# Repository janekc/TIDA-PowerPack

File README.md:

# TIDA-PowerPack
This board is designed as a prototype for powering your projects using four 18650 lithium-ion battery cells. It delivers a 5V output with a maximum current of 5A. The cells are configured in a 4S1P (4-series, 1-parallel) arrangement, balanced and charged via USB-C Power Delivery (PD) with the maximum charging current supported by the cells.
This design is based on the [TIDA-050047](https://www.ti.com/tool/TIDA-050047#design-products) reference design by Texas Instruments.

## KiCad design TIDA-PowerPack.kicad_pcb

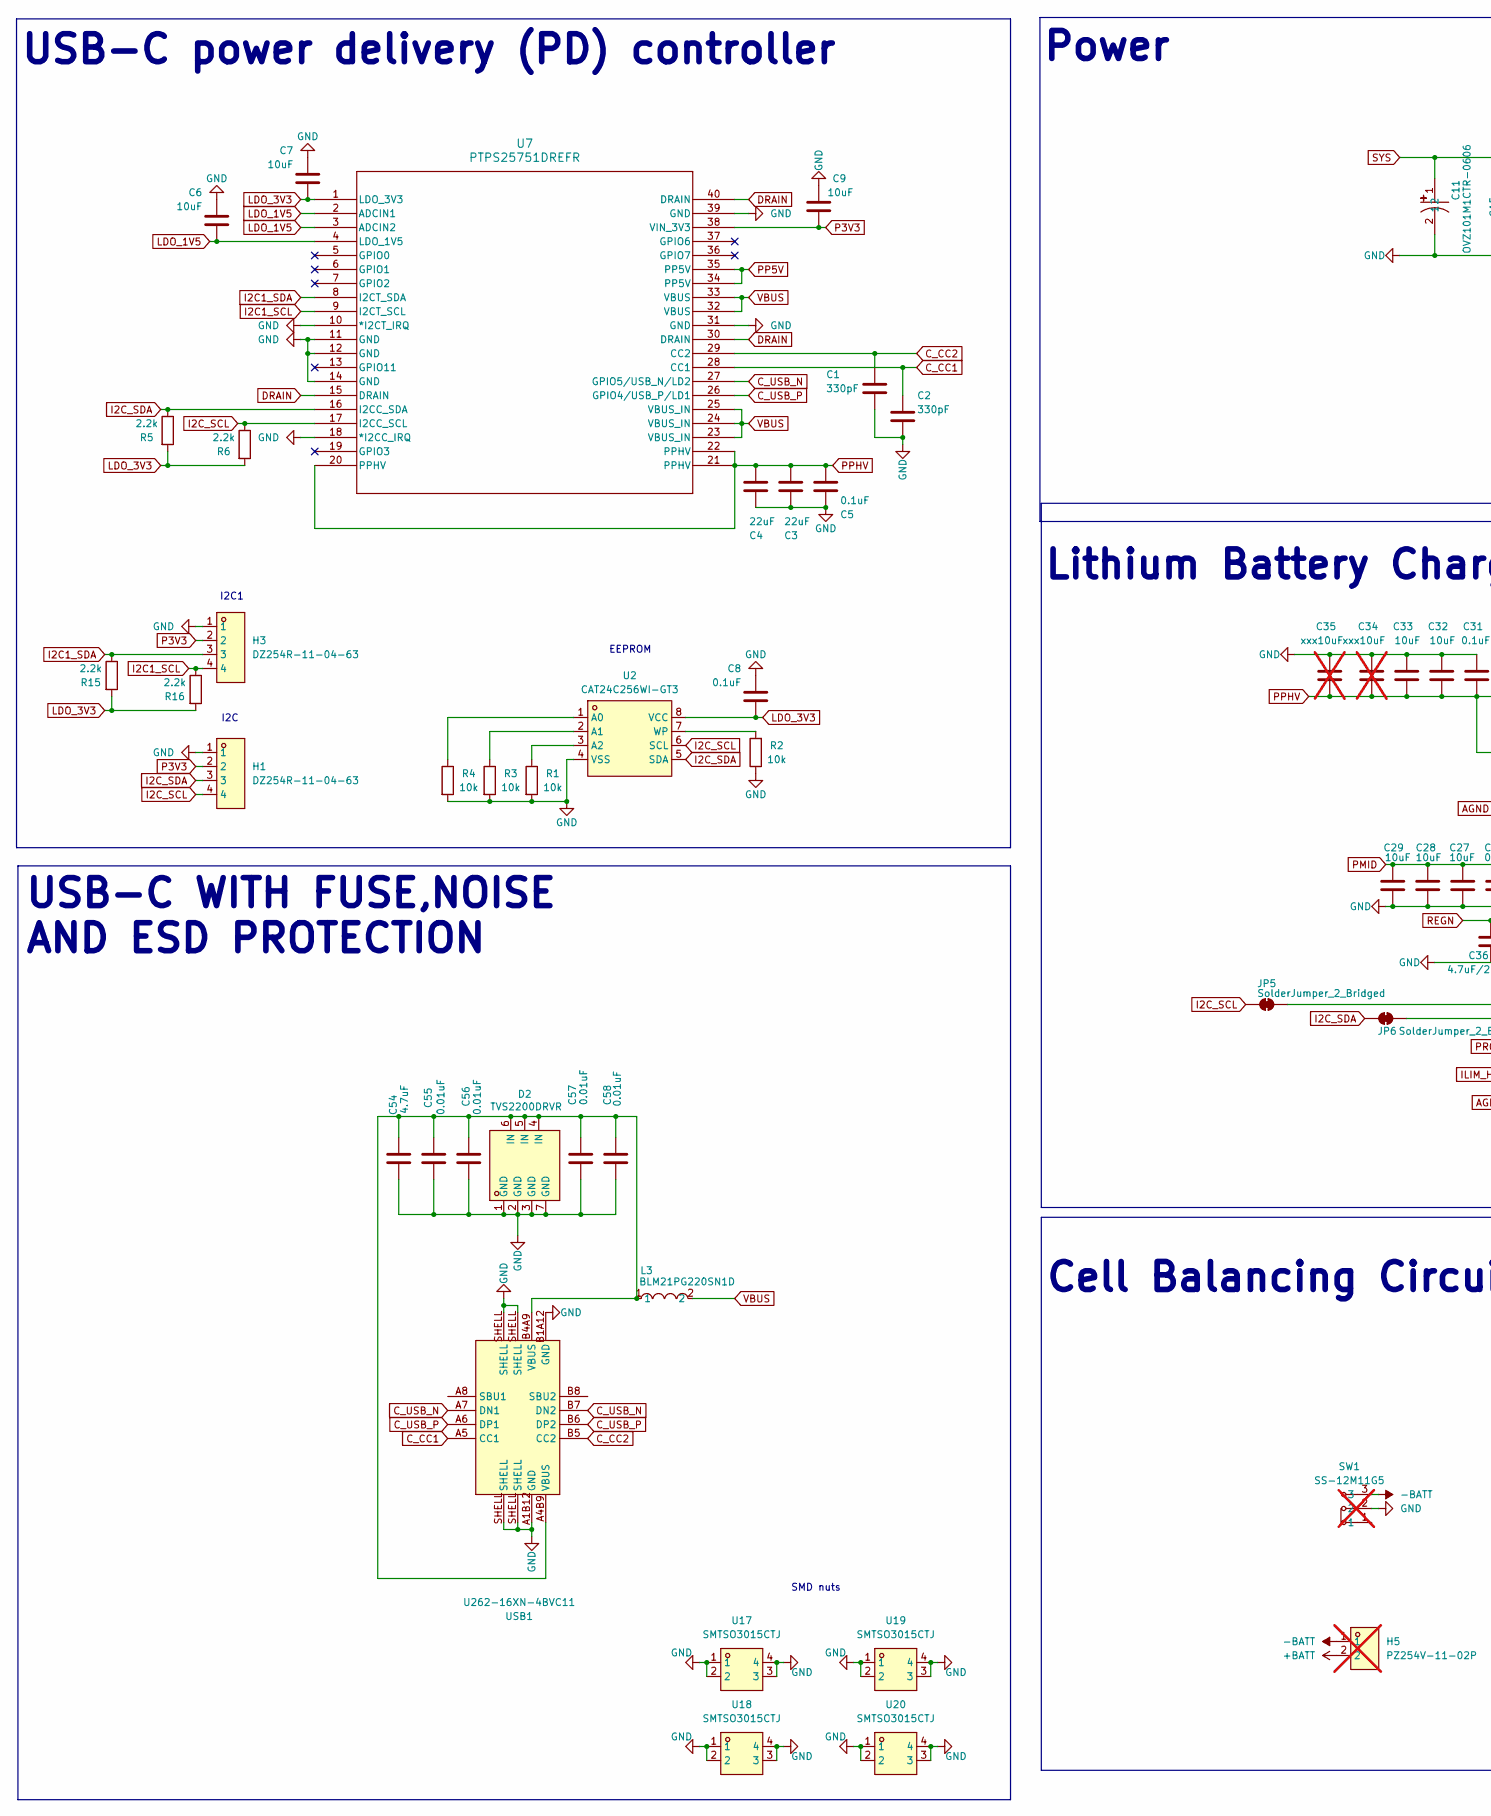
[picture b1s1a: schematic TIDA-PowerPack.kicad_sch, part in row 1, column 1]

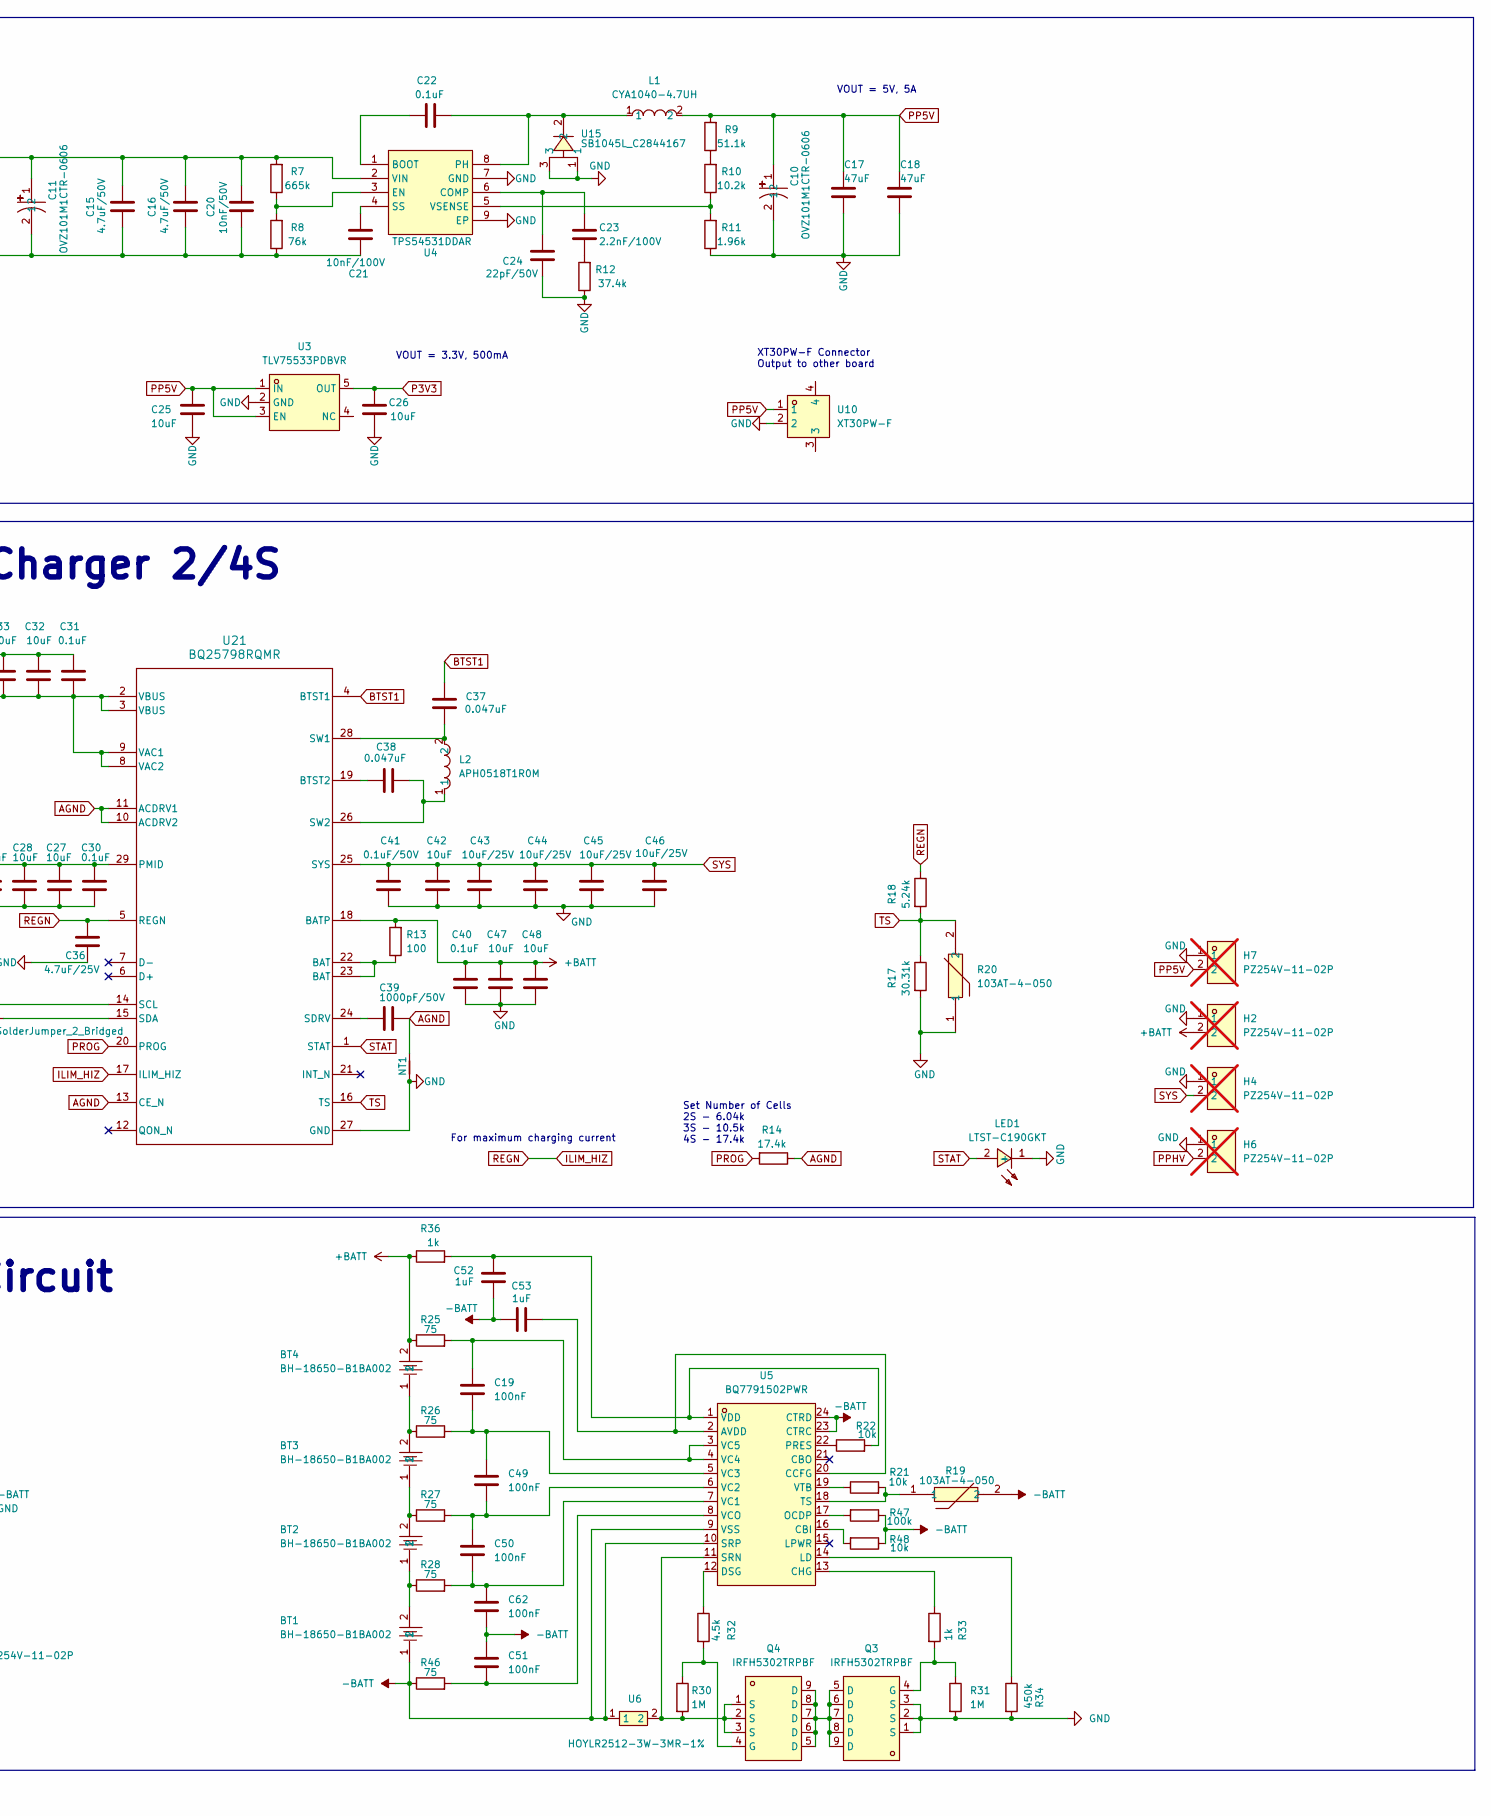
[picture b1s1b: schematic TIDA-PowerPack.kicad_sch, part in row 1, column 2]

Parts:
BT1, BT2, BT3, BT4: BH-18650-B1BA002; BATTERY-SMD_18650-1S-L77.1-W20.7-1; LCSC Part C2988620
C1, C2: 330pF; C_0603_1608Metric_Pad1.08x0.95mm_HandSolder
C3, C4: 22uF; C_0805_2012Metric_Pad1.18x1.45mm_HandSolder
C5, C8, C22, C31, C40: 0.1uF; C_0603_1608Metric_Pad1.08x0.95mm_HandSolder
C6, C7, C9, C25, C26, C27, C28, C29, C32, C33, C42, C47, C48: 10uF; C_0603_1608Metric_Pad1.08x0.95mm_HandSolder
C10, C11: OVZ101M1CTR-0606; CAP-SMD_BD6.3-L6.6-W6.6-FD-A; LCSC Part C134878
C15, C16: 4.7uF/50V; C_0805_2012Metric_Pad1.18x1.45mm_HandSolder; LCSC Part C2991173
C17, C18: 47uF; C_1206_3216Metric_Pad1.33x1.80mm_HandSolder; LCSC Part C7472975
C19, C49, C50, C51, C62: 100nF; C_0603_1608Metric_Pad1.08x0.95mm_HandSolder
C20: 10nF/50V; C_0603_1608Metric_Pad1.08x0.95mm_HandSolder
C21: 10nF/100V; C_0603_1608Metric_Pad1.08x0.95mm_HandSolder
C23: 2.2nF/100V; C_0603_1608Metric_Pad1.08x0.95mm_HandSolder
C24: 22pF/50V; C_0603_1608Metric_Pad1.08x0.95mm_HandSolder
C30: 0.1uF; C_0402_1005Metric_Pad0.74x0.62mm_HandSolder
C34, C35: xxx10uF; C_0603_1608Metric_Pad1.08x0.95mm_HandSolder; not fitted
C36: 4.7uF/25V; C_0805_2012Metric_Pad1.18x1.45mm_HandSolder; LCSC Part C2991173
C37, C38: 0.047uF; C_0603_1608Metric_Pad1.08x0.95mm_HandSolder
C39: 1000pF/50V; C_0603_1608Metric_Pad1.08x0.95mm_HandSolder
C41: 0.1uF/50V; C_0402_1005Metric_Pad0.74x0.62mm_HandSolder
C43, C44, C45, C46: 10uF/25V; C_0603_1608Metric_Pad1.08x0.95mm_HandSolder
C52: 1uF; R_0603_1608Metric_Pad0.98x0.95mm_HandSolder
C53: 1uF; C_0603_1608Metric_Pad1.08x0.95mm_HandSolder
C54: 4.7uF; C_0805_2012Metric_Pad1.18x1.45mm_HandSolder
C55, C56, C57, C58: 0.01uF; C_0603_1608Metric_Pad1.08x0.95mm_HandSolder
D2: TVS2200DRVR; WSON-6_L2.0-W2.0-P0.65-BL-EP; LCSC Part C523793
H1, H3: DZ254R-11-04-63; HDR-TH_4P-P2.54-V-M; LCSC Part C2935910
H2, H4, H5, H6, H7: PZ254V-11-02P; HDR-TH_2P-P2.54-V-M; LCSC Part C492401; not fitted
JP5, JP6: SolderJumper_2_Bridged; SolderJumper-2_P1.3mm_Bridged_RoundedPad1.0x1.5mm
L1: CYA1040-4.7UH; IND-SMD_L11.6-W10.1; LCSC Part C6364675
L2: APH0518T1R0M; IND-SMD_L5.4-W5.2; LCSC Part C5349672
L3: BLM21PG220SN1D; L0805; LCSC Part C88993
LED1: LTST-C190GKT; LED0603-RD; LCSC Part C125093
NT1: NetTie_2; SolderJumper-2_P1.3mm_Bridged2Bar_Pad1.0x1.5mm
Q3, Q4: IRFH5302TRPBF; PQFN-8_L6.0-W5.0-P1.27-LS6.0-BL; LCSC Part C148153
R1, R2, R3, R4, R21, R22, R48: 10k; R_0603_1608Metric_Pad0.98x0.95mm_HandSolder
R5, R6, R15, R16: 2.2k; R_0603_1608Metric_Pad0.98x0.95mm_HandSolder
R7: 665k; R_0603_1608Metric_Pad0.98x0.95mm_HandSolder; LCSC Part C407512
R8: 76k; R_0603_1608Metric_Pad0.98x0.95mm_HandSolder; LCSC Part C269519
R9: 51.1k; R_0603_1608Metric_Pad0.98x0.95mm_HandSolder; LCSC Part C407512
R10: 10.2k; R_0603_1608Metric_Pad0.98x0.95mm_HandSolder; LCSC Part C407512
R11: 1.96k; R_0603_1608Metric_Pad0.98x0.95mm_HandSolder; LCSC Part C407512
R12: 37.4k; R_0603_1608Metric_Pad0.98x0.95mm_HandSolder; LCSC Part C269519
R13: 100; R_0603_1608Metric_Pad0.98x0.95mm_HandSolder; LCSC Part C407512
R14: 17.4k; R_0603_1608Metric_Pad0.98x0.95mm_HandSolder; LCSC Part C407512
R17: 30.31k; R_0603_1608Metric_Pad0.98x0.95mm_HandSolder; LCSC Part C407512
R18: 5.24k; R_0603_1608Metric_Pad0.98x0.95mm_HandSolder; LCSC Part C407512
R19, R20: 103AT-4-050; RES-TH_L2.5-W2.5-P1.70-D0.3; LCSC Part C497233
R25, R26, R27, R28, R46: 75; R_1206_3216Metric_Pad1.30x1.75mm_HandSolder
R30, R31: 1M; R_0603_1608Metric_Pad0.98x0.95mm_HandSolder
R32: 4.5k; R_0603_1608Metric_Pad0.98x0.95mm_HandSolder
R33, R36: 1k; R_0603_1608Metric_Pad0.98x0.95mm_HandSolder
R34: 450k; R_0603_1608Metric_Pad0.98x0.95mm_HandSolder
R47: 100k; R_0603_1608Metric_Pad0.98x0.95mm_HandSolder
SW1: SS-12M11G5; SW-TH_XKB_SS-12M11XX; LCSC Part C2879839; not fitted
U2: CAT24C256WI-GT3; SOIC-8_L4.9-W3.9-P1.27-LS6.0-BL; LCSC Part C79987
U3: TLV75533PDBVR; SOT-23-5_L3.0-W1.7-P0.95-LS2.8-BR; LCSC Part C404027
U4: TPS54531DDAR; SOIC-8_L5.0-W4.0-P1.27-LS6.0-BL-EP2.0; LCSC Part C50605
U5: BQ7791502PWR; TSSOP-24_L7.8-W4.4-P0.65-LS6.4-BL_1; LCSC Part C2865574
U6: HOYLR2512-3W-3MR-1%; R2512; LCSC Part C5375459
U7: PTPS25751DREFR; WQFN38_REF_TEX
U10: XT30PW-F; CONN-TH_XT30PW-F-1; LCSC Part C2913282
U15: SB1045L_C2844167; TO-277_3P-L5.4-W4.0-LS6.5-TR; LCSC Part C2844167
U17, U18, U19, U20: SMTSO3015CTJ; SMTSO3030CTJ; LCSC Part C2915632
U21: BQ25798RQMR; RQM0029A-MFG
USB1: U262-16XN-4BVC11; USB-3.1-SMD_U262-161N-4BVC11; LCSC Part C319148

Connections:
+BATT: BT4.2, C40.2, C47.2, C48.2, H2.2, H5.2, R13.2, R25.1, R36.1, U21.18 (BATP)
-BATT: BT1.1, C51.1, C52.1, C53.1, C62.2, H5.1, R19.2, R46.1, R47.1, R48.1, SW1.3, U5.9 (VSS), U5.10 (SRP), U5.23 (CTRC), U5.24 (CTRD), U6.1
AGND: C39.1, NT1.1, R14.1, U21.10 (ACDRV2), U21.11 (ACDRV1), U21.13 (CE_N)
BTST1: C37.2, U21.4 (BTST1)
C_CC1: C2.1, U7.28 (CC1), USB1.A5 (CC1)
C_CC2: C1.1, U7.29 (CC2), USB1.B5 (CC2)
C_USB_N: U7.27 (GPIO5/USB_N/LD2), USB1.A7 (DN1), USB1.B7 (DN2)
C_USB_P: U7.26 (GPIO4/USB_P/LD1), USB1.A6 (DP1), USB1.B6 (DP2)
DRAIN: U7.15 (DRAIN), U7.30 (DRAIN), U7.40 (DRAIN)
GND: C1.2, C2.2, C3.2, C4.2, C5.2, C6.2, C7.2, C8.2, C9.2, C10.2, C11.2, C15.2, C16.2, C17.2, C18.2, C20.2, C21.2, C24.2, C25.2, C26.1, C27.2, C28.2, C29.2, C30.2, C31.2, C32.2, C33.2, C34.2, C35.2, C36.1, C40.1, C41.1, C42.1, C43.1, C44.1, C45.1, C46.1, C47.1, C48.1, C54.1, C55.1, C56.1, C57.1, C58.1, D2.1 (GND), D2.2 (GND), D2.3 (GND), D2.7 (GND), H1.1, H2.1, H3.1, H4.1, H6.1, H7.1, LED1.1 (-), NT1.2, Q3.1 (S), Q3.2 (S), Q3.3 (S), R1.2, R2.1, R3.2, R4.2, R8.1, R11.1, R12.1, R17.2, R20.1, R31.2, R34.2, SW1.2, U2.4 (VSS), U3.2 (GND), U4.7 (GND), U4.9 (EP), U7.10 (*I2CT_IRQ), U7.11 (GND), U7.12 (GND), U7.14 (GND), U7.18 (*I2CC_IRQ), U7.31 (GND), U7.39 (GND), U10.2, U15.1, U15.3, U17.1, U17.2, U17.3, U17.4, U18.1, U18.2, U18.3, U18.4, U19.1, U19.2, U19.3, U19.4, U20.1, U20.2, U20.3, U20.4, U21.27 (GND), USB1.A1B12 (GND), USB1.B1A12 (GND), USB1.SHELL
I2C1_SCL: H3.4, R16.1, U7.9 (I2CT_SCL)
I2C1_SDA: H3.3, R15.1, U7.8 (I2CT_SDA)
I2C_SCL: H1.4, JP5.1 (A), R6.1, U2.6 (SCL), U7.17 (I2CC_SCL)
I2C_SDA: H1.3, JP6.1 (A), R5.1, U2.5 (SDA), U7.16 (I2CC_SDA)
ILIM_HIZ: C36.2, R18.1, U21.5 (REGN), U21.17 (ILIM_HIZ)
LDO_1V5: C6.1, U7.2 (ADCIN1), U7.3 (ADCIN2), U7.4 (LDO_1V5)
LDO_3V3: C7.1, C8.1, R5.2, R6.2, R15.2, R16.2, U2.8 (VCC), U7.1 (LDO_3V3)
unnamed: BT1.2, BT2.1, R28.1
unnamed: BT2.2, BT3.1, R27.1
unnamed: BT3.2, BT4.1, R26.1
unnamed: C23.2, R12.2
unnamed: C54.2, C55.2, C56.2, C57.2, C58.2, D2.4 (IN), D2.5 (IN), D2.6 (IN), L3.1, USB1.A4B9 (VBUS), USB1.B4A9 (VBUS)
unnamed: JP5.2 (B), U21.14 (SCL)
unnamed: JP6.2 (B), U21.15 (SDA)
unnamed: Q3.5 (D), Q3.6 (D), Q3.7 (D), Q3.8 (D), Q3.9 (D), Q4.5 (D), Q4.6 (D), Q4.7 (D), Q4.8 (D), Q4.9 (D)
unnamed: Q3.4 (G), R31.1, R33.2
unnamed: Q4.4 (G), R30.1, R32.2
unnamed: R9.1, R10.2
unnamed: R13.1, U21.22 (BAT), U21.23 (BAT)
unnamed: R4.1, U2.1 (A0)
unnamed: R3.1, U2.2 (A1)
unnamed: R1.1, U2.3 (A2)
unnamed: R2.2, U2.7 (WP)
unnamed: C22.1, U4.1 (BOOT)
unnamed: C23.1, C24.1, U4.6 (COMP)
unnamed: R7.1, R8.2, U4.3 (EN)
unnamed: C22.2, L1.1, U4.8 (PH), U15.2
unnamed: C21.1, U4.4 (SS)
unnamed: R10.1, R11.2, U4.5 (VSENSE)
unnamed: C53.2, U5.2 (AVDD), U5.20 (CCFG)
unnamed: R48.2, U5.16 (CBI)
unnamed: R33.1, U5.13 (CHG)
unnamed: R32.1, U5.12 (DSG)
unnamed: R34.1, U5.14 (LD)
unnamed: R47.2, U5.17 (OCDP)
unnamed: R22.1, U5.22 (PRES)
unnamed: Q4.1 (S), Q4.2 (S), Q4.3 (S), R30.2, U5.11 (SRN), U6.2
unnamed: R19.1, R21.2, U5.18 (TS)
unnamed: C50.2, C62.1, R28.2, U5.7 (VC1)
unnamed: C49.2, C50.1, R27.2, U5.6 (VC2)
unnamed: C19.2, C49.1, R26.2, U5.5 (VC3)
unnamed: C19.1, R25.2, U5.3 (VC5), U5.4 (VC4)
unnamed: C51.2, R46.2, U5.8 (VCO)
unnamed: C52.2, R22.2, R36.2, U5.1 (VDD)
unnamed: R21.1, U5.19 (VTB)
unnamed: C38.1, U21.19 (BTST2)
unnamed: C39.2, U21.24 (SDRV)
unnamed: C37.1, L2.2, U21.28 (SW1)
unnamed: C38.2, L2.1, U21.26 (SW2)
P3V3: C9.1, C26.2, H1.2, H3.2, U3.5 (OUT), U7.38 (VIN_3V3)
PMID: C27.1, C28.1, C29.1, C30.1, U21.29 (PMID)
PP5V: C10.1, C17.1, C18.1, C25.1, H7.2, L1.2, R9.2, U3.1 (IN), U3.3 (EN), U7.34 (PP5V), U7.35 (PP5V), U10.1
PPHV: C3.1, C4.1, C5.1, C31.1, C32.1, C33.1, C34.1, C35.1, H6.2, U7.20 (PPHV), U7.21 (PPHV), U7.22 (PPHV), U21.2 (VBUS), U21.3 (VBUS), U21.8 (VAC2), U21.9 (VAC1)
PROG: R14.2, U21.20 (PROG)
STAT: LED1.2 (+), U21.1 (STAT)
SYS: C11.1, C15.1, C16.1, C20.1, C41.2, C42.2, C43.2, C44.2, C45.2, C46.2, H4.2, R7.2, U4.2 (VIN), U21.25 (SYS)
TS: R17.1, R18.2, R20.2, U21.16 (TS)
VBUS: L3.2, U7.23 (VBUS_IN), U7.24 (VBUS_IN), U7.25 (VBUS_IN), U7.32 (VBUS), U7.33 (VBUS)

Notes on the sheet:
Cell Balancing Circuit
Lithium Battery Charger 2/4S
SMD nuts
VOUT = 3.3V, 500mA
XT30PW-F Connector Output to other board
USB-C WITH FUSE,NOISE AND ESD PROTECTION
I2C
Power
I2C1
For maximum charging current
USB-C power delivery (PD) controller
EEPROM
Set Number of Cells 2S - 6.04k 3S - 10.5k 4S - 17.4k
VOUT = 5V, 5A

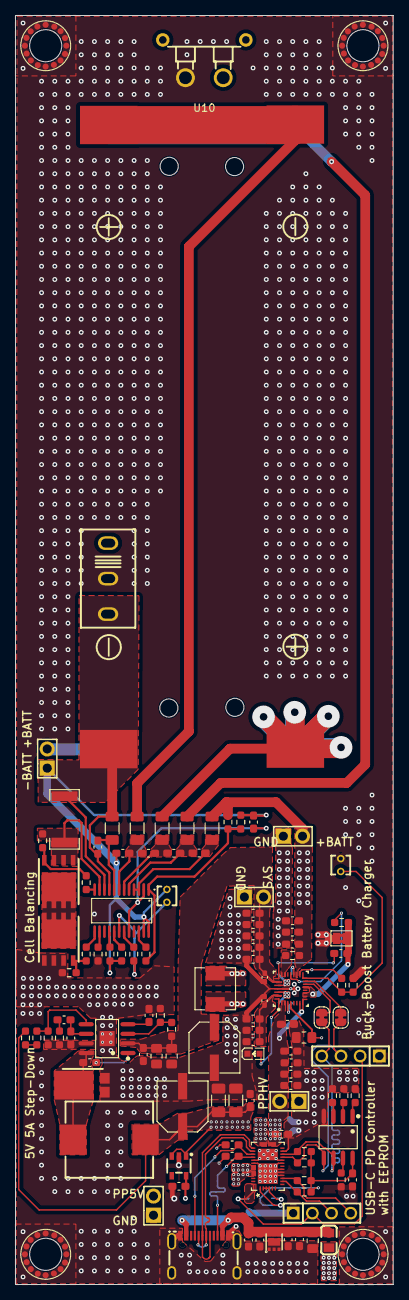
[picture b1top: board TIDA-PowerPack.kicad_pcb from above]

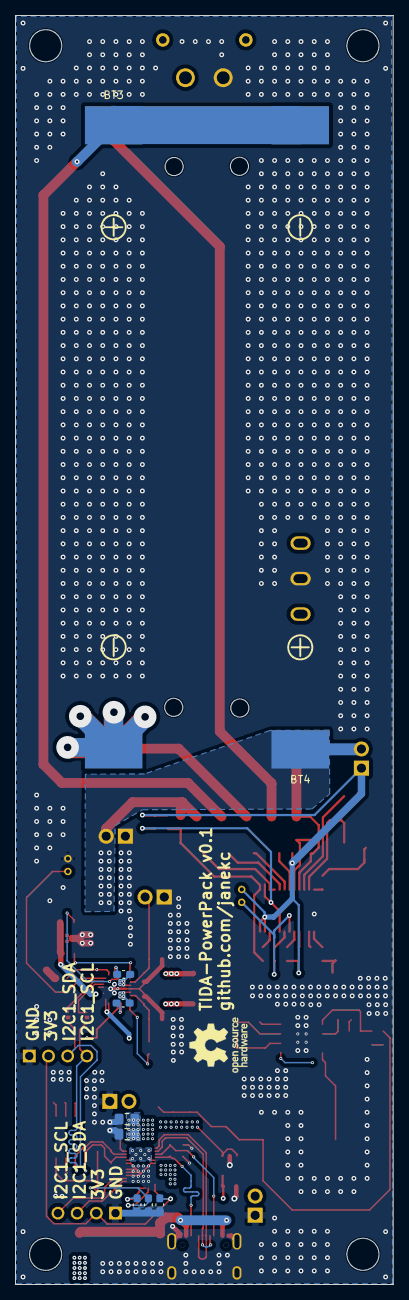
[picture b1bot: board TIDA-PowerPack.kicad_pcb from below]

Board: 4 copper layers, 50.0 x 168.0 mm, 127 parts (9 on the bottom side), 68 nets.

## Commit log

2024-05-18 export schematics
2024-06-02 update from fiver
2024-06-06 update schematics, add cell monitors that switches cells off if something is wrong, started pcb layout
2024-10-10 rearrange charger components
2024-10-11 use recommended layout by ti
2024-10-11 fix commit
2024-10-12 fix zones with via stiching
2025-04-04 add pcb layout using the layout guidelines froms the texas instruments ICs
2025-04-07 replace battery protection with IC that actually balances the cells
2025-04-07 enlarge silkscreen font
2025-04-07 rename project to TIDA-PowerPack
2025-04-07 add gerber files
2025-04-07 ordered prototype
2025-04-08 add 3d models
2025-04-08 add 3d model
2025-04-08 replace TPS25750D with TPS25751 chip
2025-04-08 add picture
